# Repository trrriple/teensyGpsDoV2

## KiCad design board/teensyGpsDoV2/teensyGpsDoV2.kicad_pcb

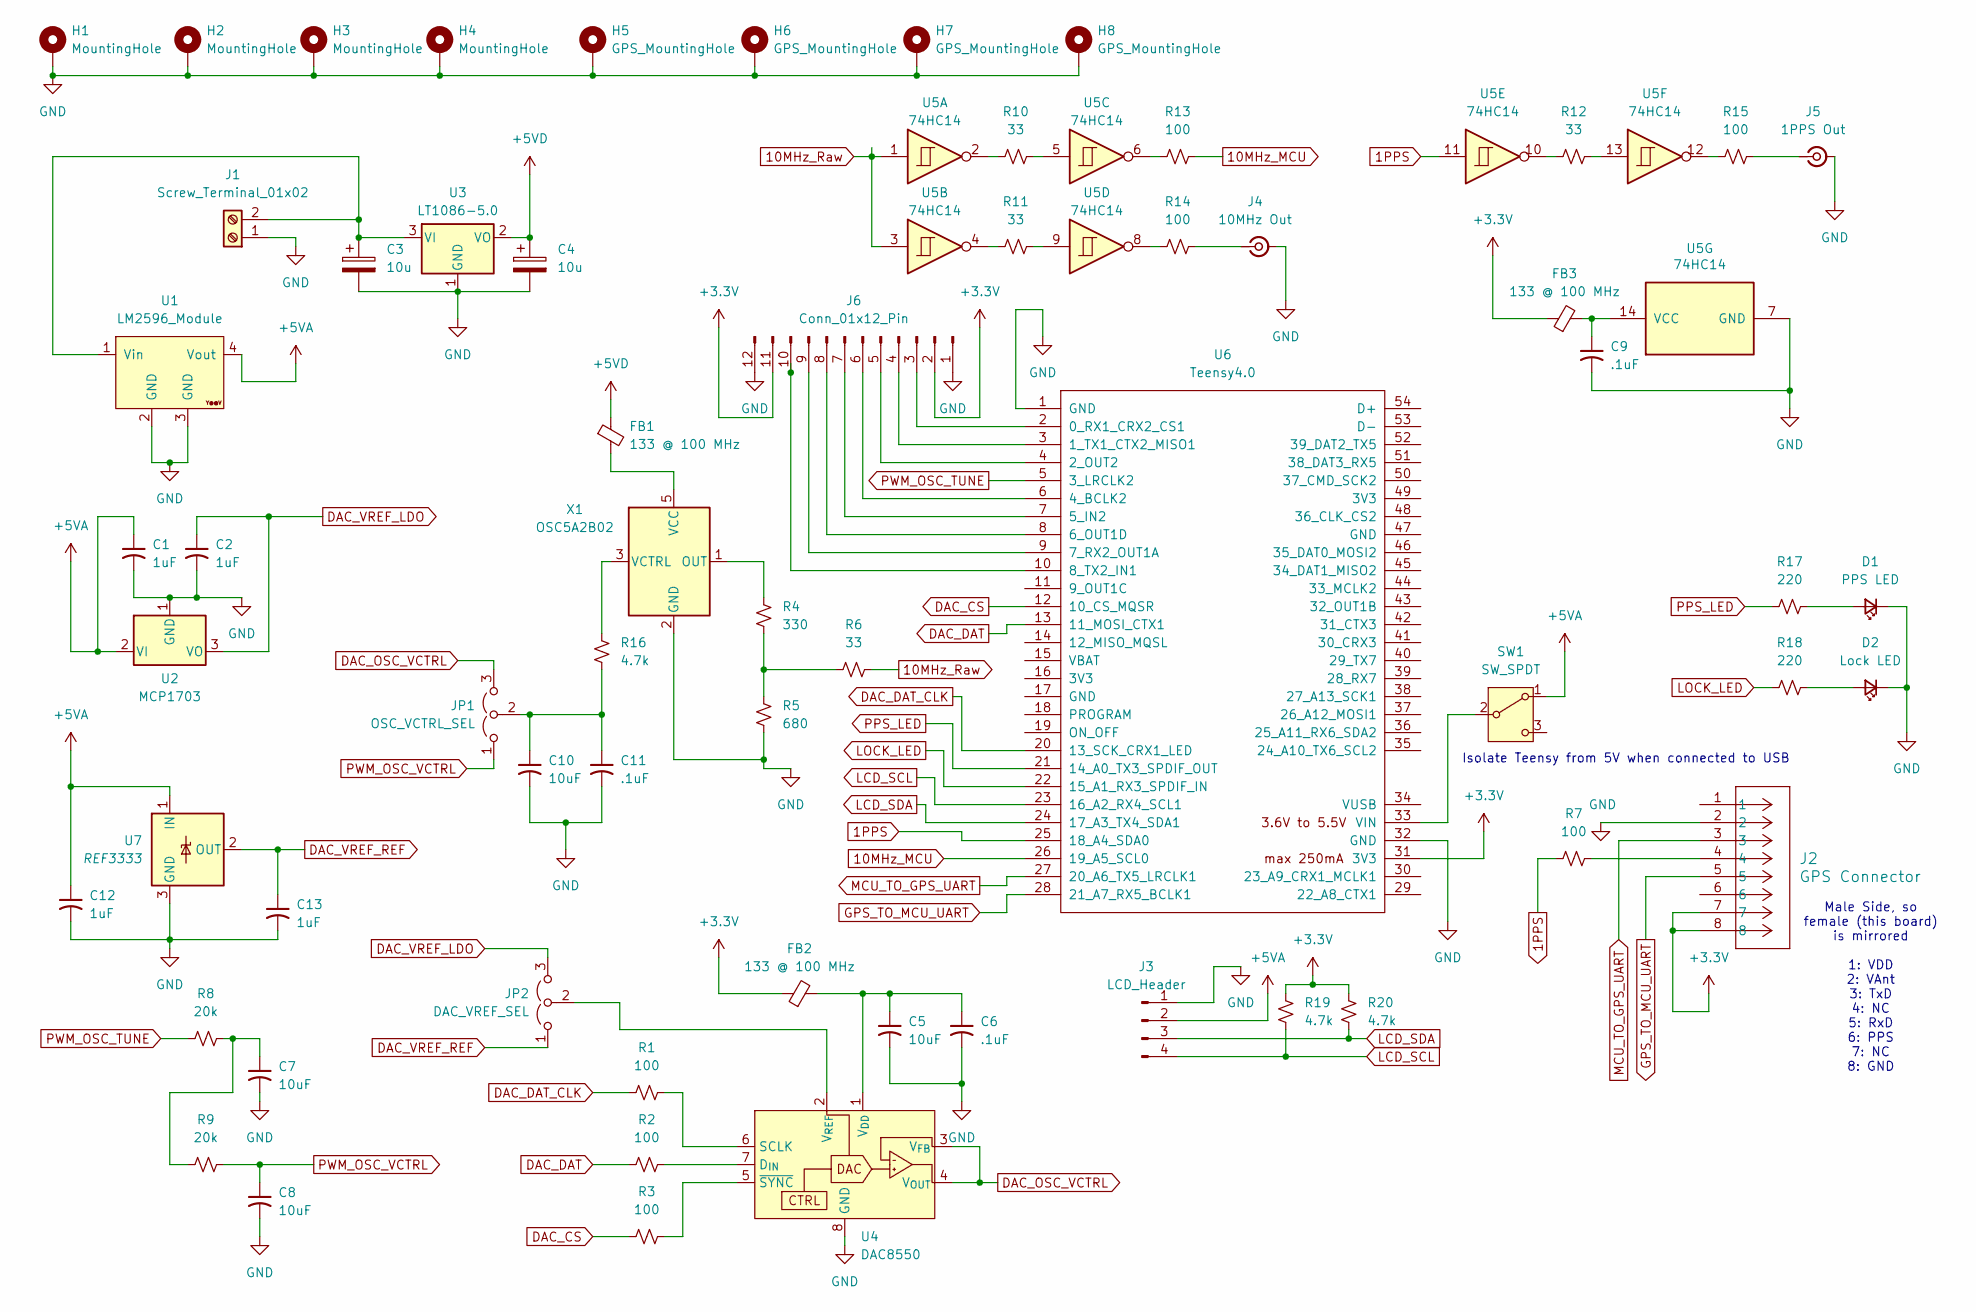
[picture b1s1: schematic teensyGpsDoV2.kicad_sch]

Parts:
C1, C2, C12, C13: 1uF; C_Disc_D5.0mm_W2.5mm_P5.00mm
C3, C4: 10u; CP_Radial_Tantal_D5.0mm_P5.00mm
C5, C7, C8, C10: 10uF; C_Disc_D5.0mm_W2.5mm_P5.00mm
C6, C9, C11: .1uF; C_Disc_D5.0mm_W2.5mm_P5.00mm
D1: PPS LED; LED_D5.0mm_Clear
D2: Lock LED; LED_D5.0mm_Clear
FB1, FB2, FB3: 133 @ 100 MHz; R_Axial_DIN0411_L9.9mm_D3.6mm_P12.70mm_Horizontal
H1, H2, H3, H4: MountingHole; MountingHole_3.5mm_Pad
H5, H6, H7, H8: GPS_MountingHole; MountingHole_3.2mm_M3_DIN965_Pad
J1: Screw_Terminal_01x02; TerminalBlock_MaiXu_MX126-5.0-02P_1x02_P5.00mm
J2: GPS Connector; CONN4x2_NPPN042AFCN-RC_SUL
J3: LCD_Header; PinHeader_1x04_P2.54mm_Vertical
J4: 10MHz Out; CONN_RF2-04A-T-00-50-G_ADM
J5: 1PPS Out; CONN_RF2-04A-T-00-50-G_ADM
J6: Conn_01x12_Pin; PinHeader_1x12_P2.54mm_Vertical
JP1: OSC_VCTRL_SEL; PinHeader_1x03_P2.54mm_Vertical
JP2: DAC_VREF_SEL; PinHeader_1x03_P2.54mm_Vertical
R1, R2, R3, R7, R13, R14, R15: 100; R_Axial_DIN0207_L6.3mm_D2.5mm_P10.16mm_Horizontal
R4: 330; R_Axial_DIN0207_L6.3mm_D2.5mm_P10.16mm_Horizontal
R5: 680; R_Axial_DIN0207_L6.3mm_D2.5mm_P10.16mm_Horizontal
R6, R10, R11, R12: 33; R_Axial_DIN0207_L6.3mm_D2.5mm_P10.16mm_Horizontal
R8, R9: 20k; R_Axial_DIN0207_L6.3mm_D2.5mm_P10.16mm_Horizontal
R16, R19, R20: 4.7k; R_Axial_DIN0207_L6.3mm_D2.5mm_P10.16mm_Horizontal
R17, R18: 220; R_Axial_DIN0207_L6.3mm_D2.5mm_P10.16mm_Horizontal
SW1: SW_SPDT; PinHeader_1x03_P2.54mm_Vertical
U1: LM2596_Module; YAAJ_DCDC_StepDown_LM2596
U2: MCP1703; TO-92_Inline
U3: LT1086-5.0; TO-220-3_Vertical
U4: DAC8550; VSSOP-8_3x3mm_P0.65mm
U5: 74HC14; DIP-14_W7.62mm_Socket
U6: Teensy4.0; Teensy40
U7: REF3333; SOT-23
X1: OSC5A2B02; CTI-OSC-25x25

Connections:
1PPS: R7.1, U5.11, U6.25 (18_A4_SDA0)
10MHz_MCU: R13.2, U6.26 (19_A5_SCL0)
10MHz_Raw: R6.2, U5.1, U5.3
+3.3V: FB2.1, FB3.1, J2.7, J2.8, J6.2, J6.11, R19.1, R20.1, U6.31 (3V3)
+5VA: C1.1, C12.1, J3.2, SW1.1 (A), U1.4 (Vout), U2.2 (VI), U7.1 (IN)
+5VD: C4.1, FB1.1, U3.2 (VO)
DAC_CS: R3.1, U6.12 (10_CS_MQSR)
DAC_DAT: R2.1, U6.13 (11_MOSI_CTX1)
DAC_DAT_CLK: R1.1, U6.20 (13_SCK_CRX1_LED)
DAC_OSC_VCTRL: JP1.3 (B), U4.3 (V_{FB}), U4.4 (V_{OUT})
DAC_VREF_LDO: C2.1, JP2.3 (B), U2.3 (VO)
DAC_VREF_REF: C13.1, JP2.1 (A), U7.2 (OUT)
GND: C1.2, C2.2, C3.2, C4.2, C5.2, C6.2, C7.2, C8.2, C9.2, C10.2, C11.2, C12.2, C13.2, D1.1 (K), D2.1 (K), H1.1, H2.1, H3.1, H4.1, H5.1, H6.1, H7.1, H8.1, J1.1, J2.2, J3.1, J4.2 (Ext), J5.2 (Ext), J6.1, J6.12, R5.2, U1.2 (GND), U1.3 (GND), U2.1 (GND), U3.1 (GND), U4.8 (GND), U5.7 (GND), U6.1 (GND), U6.32 (GND), U7.3 (GND), X1.2 (GND)
GPS_TO_MCU_UART: J2.5, U6.28 (21_A7_RX5_BCLK1)
LCD_SCL: J3.4, R19.2, U6.23 (16_A2_RX4_SCL1)
LCD_SDA: J3.3, R20.2, U6.24 (17_A3_TX4_SDA1)
LOCK_LED: R18.1, U6.22 (15_A1_RX3_SPDIF_IN)
MCU_TO_GPS_UART: J2.3, U6.27 (20_A6_TX5_LRCLK1)
unnamed: C7.1, R8.1, R9.1
unnamed: D1.2 (A), R17.2
unnamed: D2.2 (A), R18.2
unnamed: C3.1, J1.2, U1.1 (Vin), U3.3 (VI)
unnamed: J2.4, R7.2
unnamed: J4.1 (In), R14.2
unnamed: J5.1 (In), R15.2
unnamed: J6.3, U6.2 (0_RX1_CRX2_CS1)
unnamed: J6.4, U6.3 (1_TX1_CTX2_MISO1)
unnamed: J6.5, U6.4 (2_OUT2)
unnamed: J6.6, U6.6 (4_BCLK2)
unnamed: J6.7, U6.7 (5_IN2)
unnamed: J6.8, U6.8 (6_OUT1D)
unnamed: J6.9, U6.9 (7_RX2_OUT1A)
unnamed: J6.10, U6.10 (8_TX2_IN1)
unnamed: C10.1, C11.1, JP1.2 (C), R16.2
unnamed: JP2.2 (C), U4.2 (V_{REF})
unnamed: R4.2, R5.1, R6.1
unnamed: R10.1, U5.2
unnamed: R10.2, U5.5
unnamed: R11.1, U5.4
unnamed: R11.2, U5.9
unnamed: R12.1, U5.10
unnamed: R12.2, U5.13
unnamed: R13.1, U5.6
unnamed: R14.1, U5.8
unnamed: R15.1, U5.12
unnamed: SW1.2 (B), U6.33 (VIN)
unnamed: R2.2, U4.7 (D_{IN})
unnamed: R1.2, U4.6 (SCLK)
unnamed: C5.1, C6.1, FB2.2, U4.1 (V_{DD})
unnamed: R3.2, U4.5 (~SYNC)
unnamed: C9.1, FB3.2, U5.14 (VCC)
unnamed: R4.1, X1.1 (OUT)
unnamed: FB1.2, X1.5 (VCC)
unnamed: R16.1, X1.3 (VCTRL)
PPS_LED: R17.1, U6.21 (14_A0_TX3_SPDIF_OUT)
PWM_OSC_TUNE: R8.2, U6.5 (3_LRCLK2)
PWM_OSC_VCTRL: C8.1, JP1.1 (A), R9.2

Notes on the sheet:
Male Side, so female (this board) is mirrored 1: VDD 2: VAnt 3: TxD 4: NC 5: RxD 6: PPS 7: NC 8: GND
Isolate Teensy from 5V when connected to USB

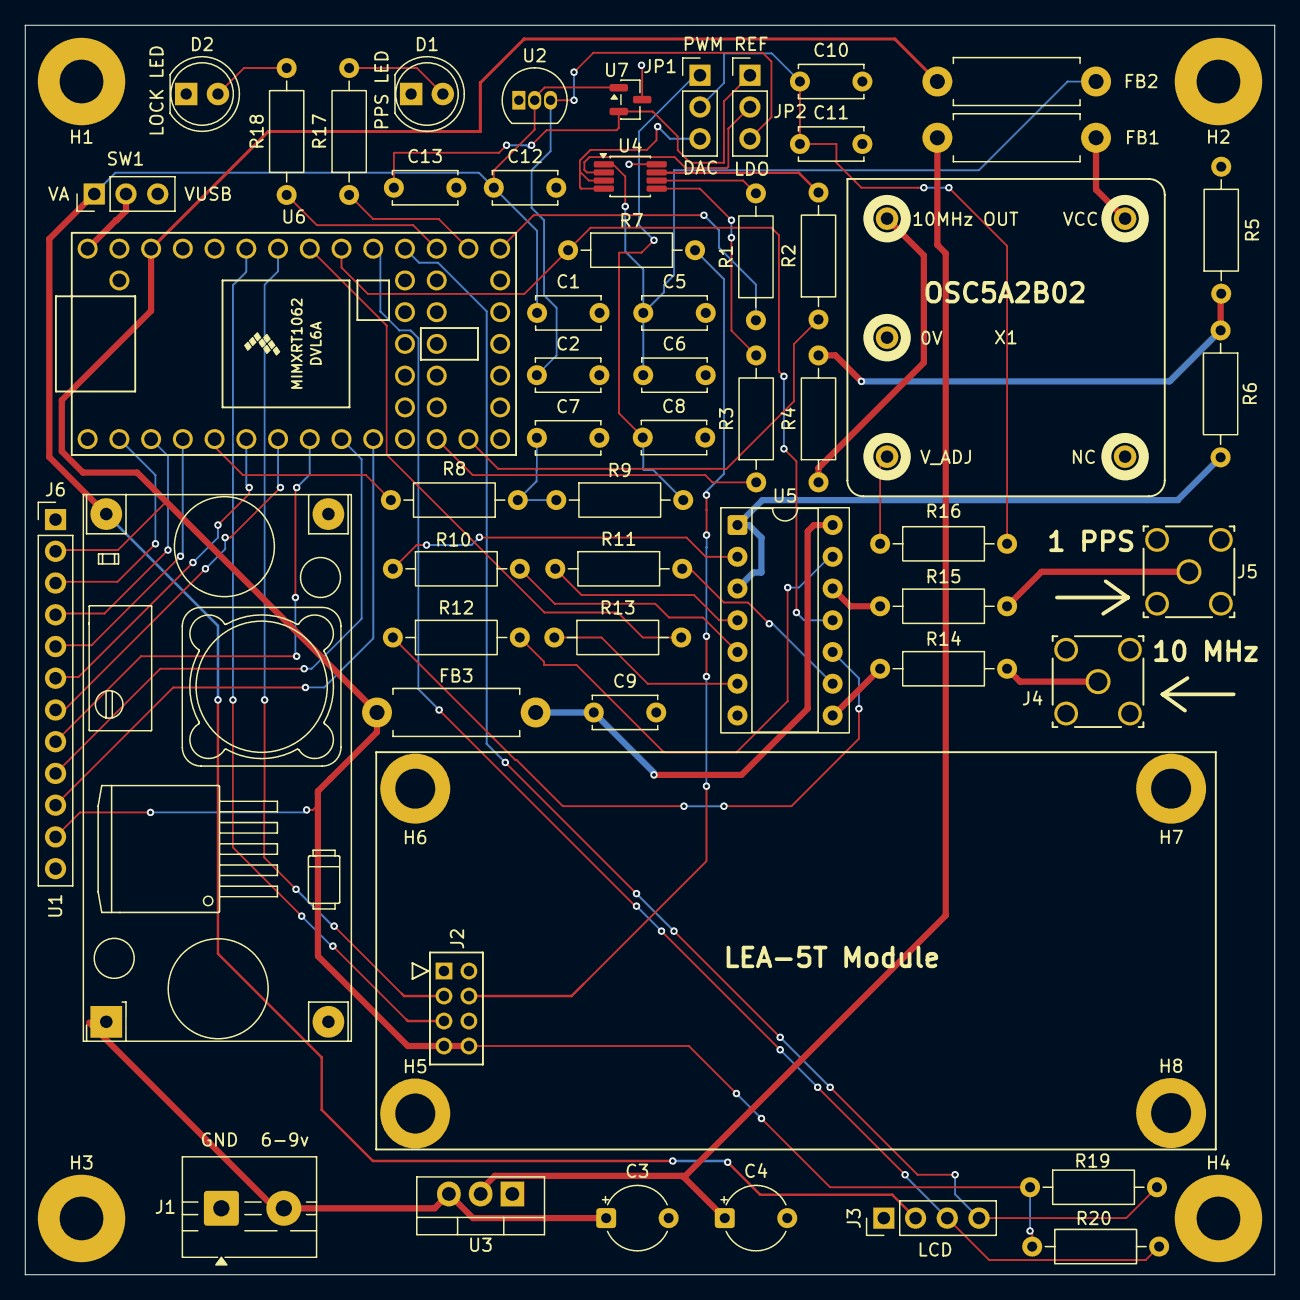
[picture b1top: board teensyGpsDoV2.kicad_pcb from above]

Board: 2 copper layers, 100.0 x 100.0 mm, 63 parts (0 on the bottom side), 57 nets.

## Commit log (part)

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2025-10-18 survey-in enable/disable logic
2025-10-19 WIP, dac8550 and oscillator tuning implemented. Tuning filter probably needs some work
2025-10-20 WIP schematic, WIP tuning code
2025-10-20 rework to use quad timer capture instead of interrupt
2025-10-21 fixed bug with counter reset value, unifying console printing to one function
2025-10-21 refinment to tuning code. Add rolling average metrics
2025-10-21 cleanup
2025-10-21 Schematic WIP
2025-10-23 WIP, moved libraries to allow wire1 instead of wire modification. Lots of tuning. LCD optimations
2025-10-23 more tuning optimization
2025-10-25 improvements
2025-10-25 wip, handle gps data data validity better
2025-10-27 mobile update
2025-10-27 wip on schematic. Added PWM option instead of DAC
2025-10-28 layout wip
2025-10-28 wip schematic, routing
2025-10-29 schematic routing done, allegedly
2025-10-29 revision 1.0 submitted for manufacturing
2025-11-07 fix PWM to be on correct pin
2025-11-14 tuning update
2025-11-14 remove redundant state variables
2025-11-15 more redunant clean up
